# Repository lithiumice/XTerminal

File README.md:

## 说明
- 模拟器工程在XTerminal\2.Software\XTerminal-ESP32-simulator
- 模拟器工程使用Visual Studio 2019
- 代码工程在XTerminal\2.Software\XTerminal-ESP32-simulator
- 代码工程基于Platformio

#
PCB在项目工程的1.Hardware中，使用Kicad绘制。分为主控板和音频板，两者的硬件连接没有设计好，实际焊接为了便于组装就用了粗一点的飞线把主控板和音频板上的sd卡引脚和音频信号引脚连了起来，我只做了临时的用于验证的一个版本，后面没有心情完善了，只能说这只用于抛砖引玉。
#

#### 主控板焊接

#### 音频板焊接

#### 焊接和组装完成的成品效果：

#### 主界面：（没拍实物图，就只好放模拟器的截图了）

#### 天气显示：

#### 几个Arduboy小游戏

#### PCB示例

#### 原理图示例

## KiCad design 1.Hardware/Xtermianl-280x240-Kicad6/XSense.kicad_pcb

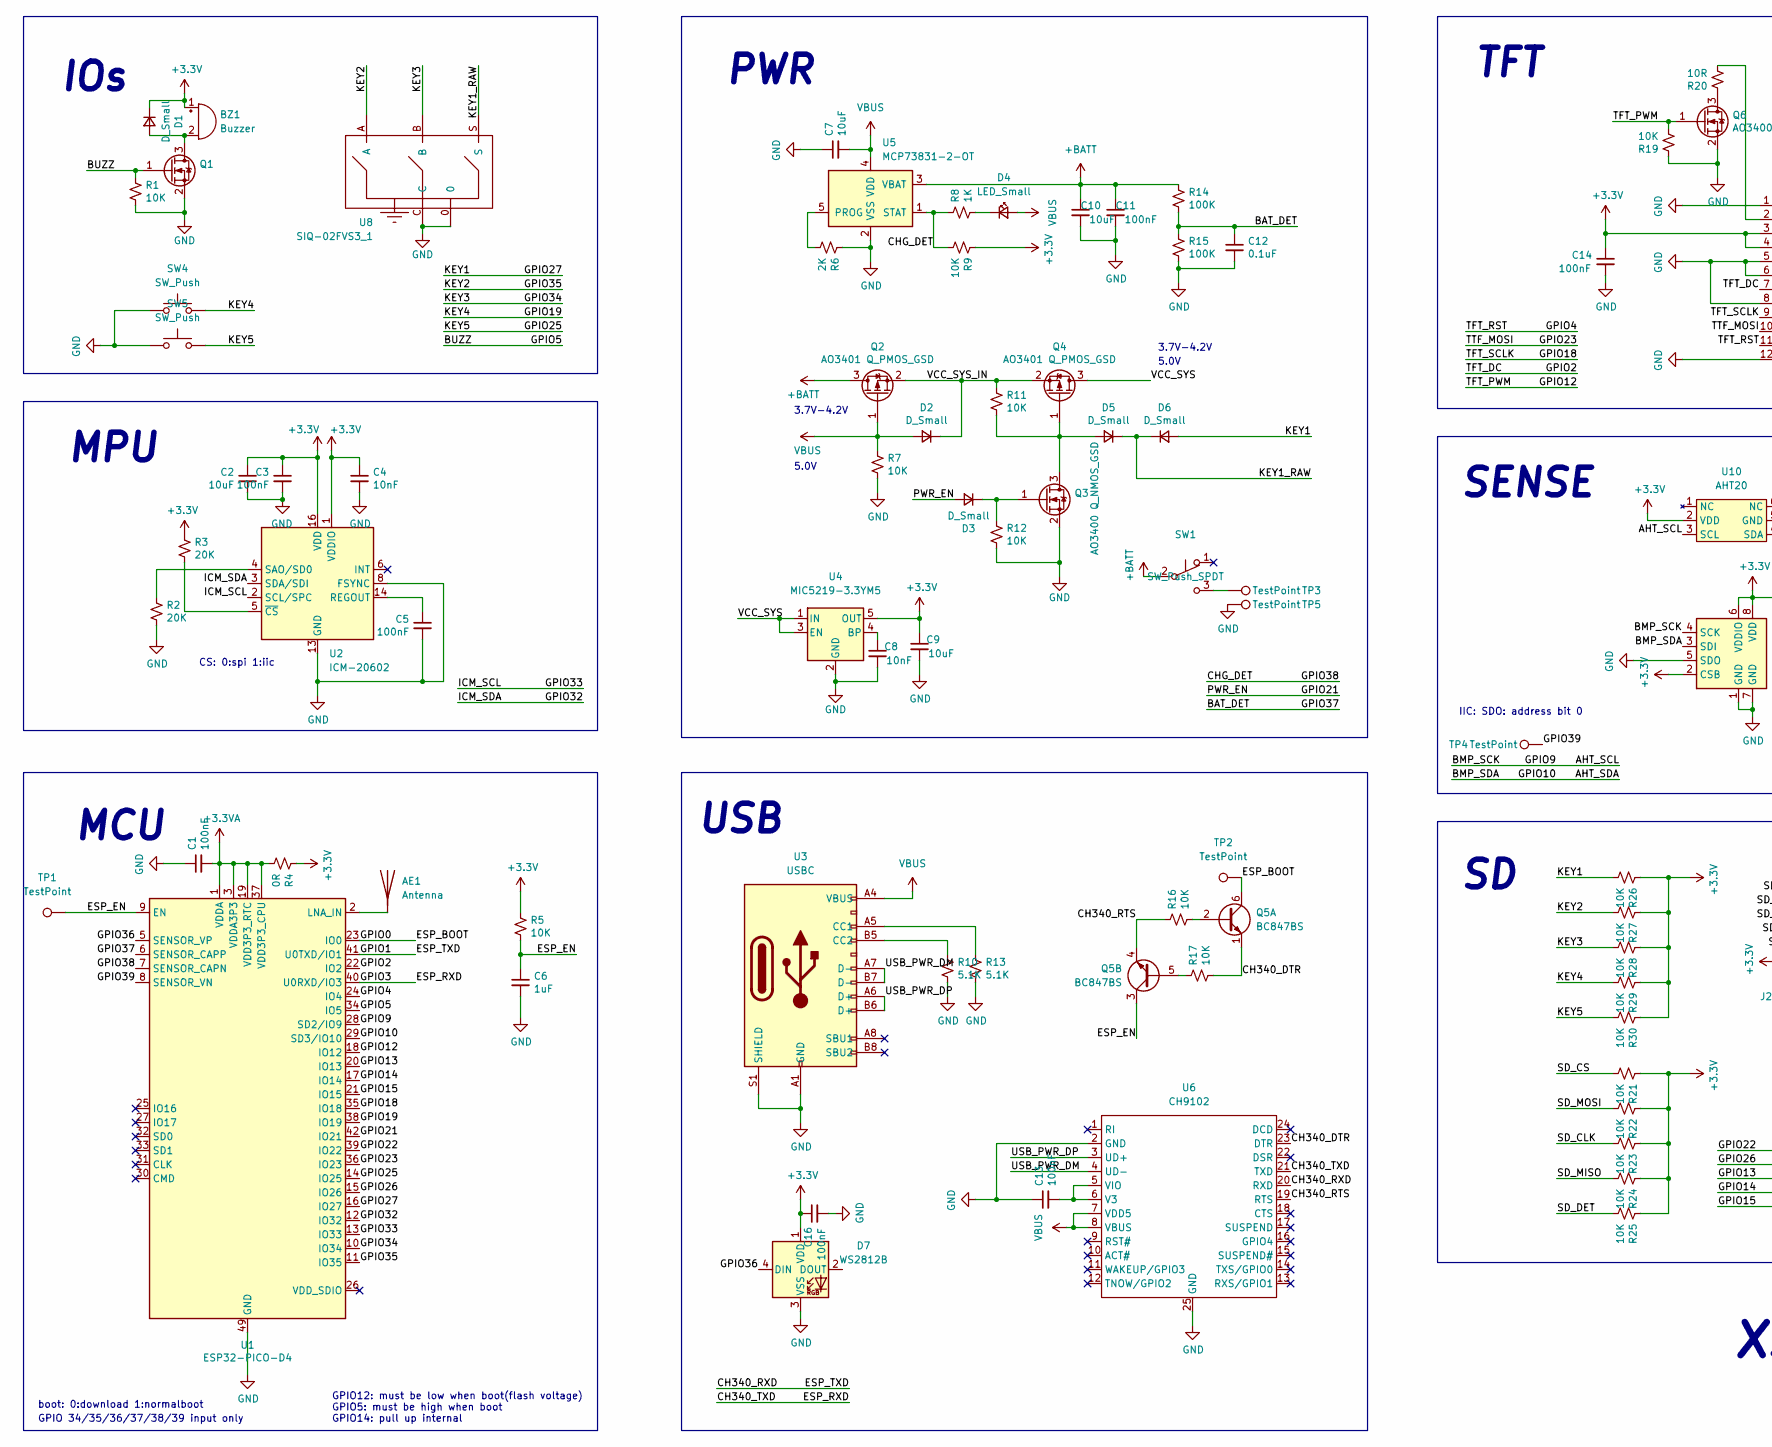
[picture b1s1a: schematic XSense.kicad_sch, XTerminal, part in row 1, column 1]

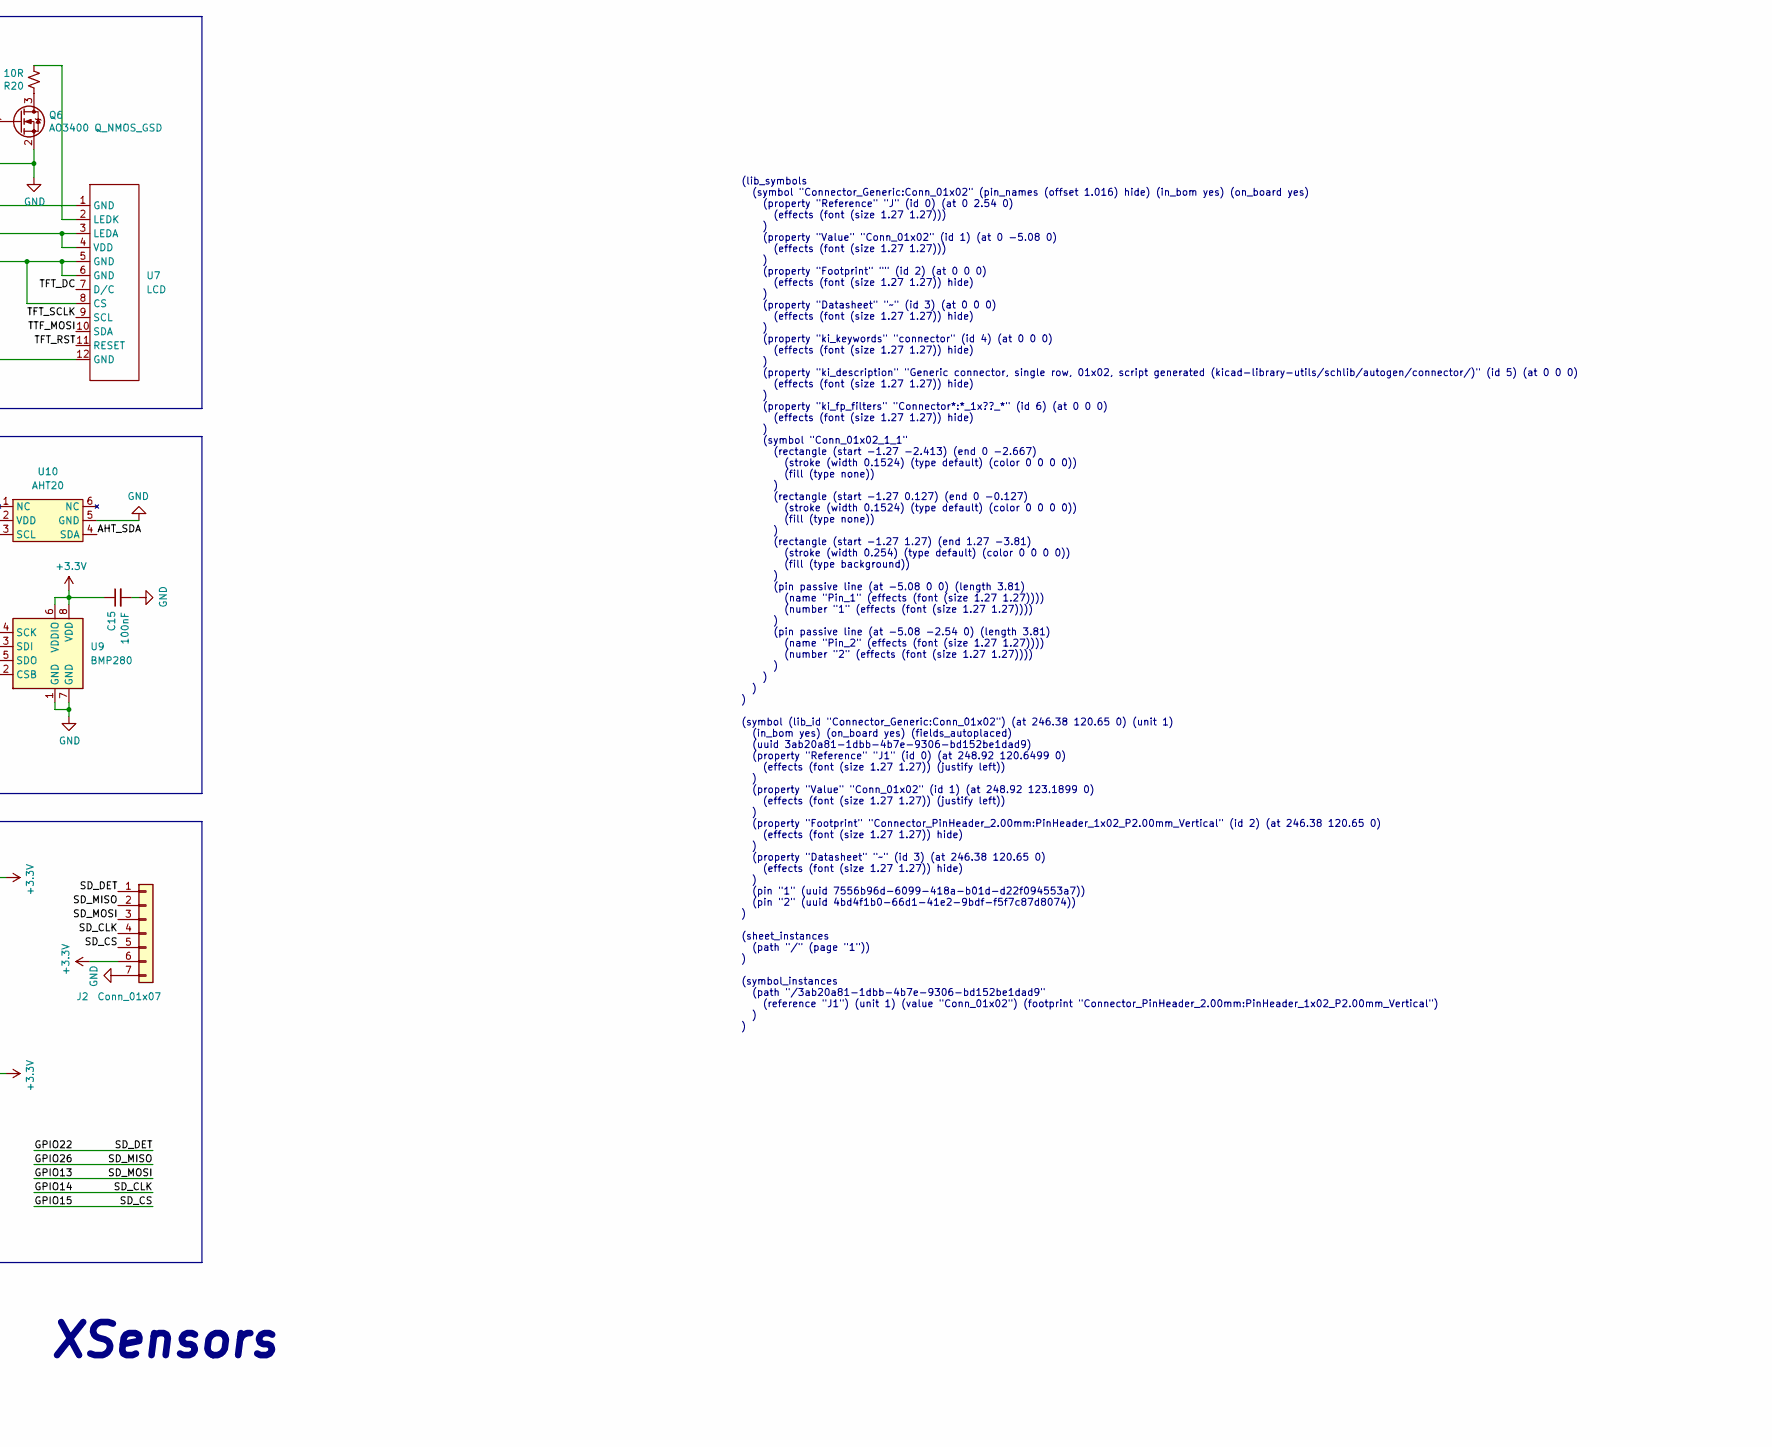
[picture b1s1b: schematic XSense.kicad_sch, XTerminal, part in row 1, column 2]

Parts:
AE1: Antenna; Johanson_2450AT43F0100
BZ1: Buzzer; DET402
C1, C3, C5, C11, C13, C14, C15, C16: 100nF; C_0402_1005Metric_Pad0.74x0.62mm_HandSolder
C2, C7, C9, C10: 10uF; C_0402_1005Metric_Pad0.74x0.62mm_HandSolder
C4, C8: 10nF; C_0402_1005Metric_Pad0.74x0.62mm_HandSolder
C6: 1uF; C_0402_1005Metric_Pad0.74x0.62mm_HandSolder
C12: 0.1uF; C_0402_1005Metric_Pad0.74x0.62mm_HandSolder
D1, D2, D3, D5, D6: D_Small; D_SOD-323
D4: LED_Small; C_0402_1005Metric_Pad0.74x0.62mm_HandSolder
D7: WS2812B; WS2812B-clear
J2: Conn_01x07; PinHeader_2x04_P2.00mm_Vertical
Q1, Q3, Q6: AO3400 Q_NMOS_GSD; SOT-23
Q2, Q4: AO3401 Q_PMOS_GSD; SOT-23
Q5: BC847BS; SOT-363_SC-70-6
R1, R5, R7, R9, R11, R12, R16, R17, R19, R21, R22, R23, R24, R25, R26, R27, R28, R29, R30: 10K; R_0402_1005Metric_Pad0.72x0.64mm_HandSolder
R2, R3: 20K; R_0402_1005Metric_Pad0.72x0.64mm_HandSolder
R4: 0R; R_0402_1005Metric_Pad0.72x0.64mm_HandSolder
R6: 2K; R_0402_1005Metric_Pad0.72x0.64mm_HandSolder
R8: 1K; R_0402_1005Metric_Pad0.72x0.64mm_HandSolder
R10, R13: 5.1K; R_0402_1005Metric_Pad0.72x0.64mm_HandSolder
R14, R15: 100K; R_0402_1005Metric_Pad0.72x0.64mm_HandSolder
R20: 10R; R_0402_1005Metric_Pad0.72x0.64mm_HandSolder
SW1: SW_Push_SPDT; SW_SPDT_PCM12
SW4, SW5: SW_Push; Panasonic_EVQPUJ_EVQPUA
TP1, TP2, TP3, TP4, TP5: TestPoint; TestPoint_Pad_D1.0mm
U1: ESP32-PICO-D4; QFN-48-7x7mm
U2: ICM-20602; LGA-16_3x3mm_P0.5mm_LayoutBorder3x5y
U3: USBC; USB_C_Receptacle_XKB_U262-16XN-4BVC11
U4: MIC5219-3.3YM5; SOT-23-5
U5: MCP73831-2-OT; SOT-23-5
U6: CH9102; QFN-24-1EP_4x4mm_P0.5mm_EP2.15x2.15mm
U7: LCD; LCD-ST7789-1.54-12PINS
U8: SIQ-02FVS3_1; SW-SMD_SIQ-02FVS3_1
U9: BMP280; Bosch_LGA-8_2x2.5mm_P0.65mm_ClockwisePinNumbering
U10: AHT20; DFN-6-1EP_3x3mm_P1mm_EP1.5x2.4mm

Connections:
+3.3VA: C1.2, R4.2, U1.1 (VDDA), U1.3 (VDDA3P3), U1.4 (VDDA3P3), U1.19 (VDD3P3_RTC), U1.37 (VDD3P3_CPU), U1.43 (VDDA), U1.46 (VDDA)
+3V3: BZ1.1 (-), C2.1, C3.1, C4.1, C9.1, C14.1, C15.1, C16.1, D1.1 (K), D7.1 (VDD), J2.6, R3.1, R4.1, R5.1, R9.1, R21.1, R22.1, R23.1, R24.1, R25.1, R26.1, R27.1, R28.1, R29.1, R30.1, U2.1 (VDDIO), U2.16 (VDD), U4.5 (OUT), U7.3 (LEDA), U7.4 (VDD), U9.2 (CSB), U9.6 (VDDIO), U9.8 (VDD), U10.2 (VDD)
+BATT: C10.1, C11.1, Q2.3 (D), R14.1, SW1.2 (B), U5.3 (VBAT)
/AHT_SCL: U1.28 (SD2/IO9), U9.4 (SCK), U10.3 (SCL)
/AHT_SDA: U1.29 (SD3/IO10), U9.3 (SDI), U10.4 (SDA)
/BAT_DET: C12.1, R14.2, R15.1, U1.6 (SENSOR_CAPP)
/BUZZ: Q1.1 (G), R1.1, U1.34 (IO5)
/CH340_DTR: Q5.1 (E1), R17.2, U6.23 (DTR)
/CH340_RTS: Q5.4 (E2), R16.1, U6.19 (RTS)
/CH340_RXD: U1.41 (U0TXD/IO1), U6.20 (RXD)
/CH340_TXD: U1.40 (U0RXD/IO3), U6.21 (TXD)
/CHG_DET: R8.1, R9.2, U1.7 (SENSOR_CAPN), U5.1 (STAT)
/ESP_BOOT: Q5.6 (C1), TP2.1, U1.23 (IO0)
/ESP_EN: C6.1, Q5.3 (C2), R5.2, TP1.1, U1.9 (EN)
/GPIO2: U1.22 (IO2), U7.7 (D/C)
/GPIO4: U1.24 (IO4), U7.11 (RESET)
/GPIO12: Q6.1 (G), R19.2, U1.18 (IO12)
/GPIO13: J2.3, R22.2, U1.20 (IO13)
/GPIO14: J2.4, R23.2, U1.17 (IO14)
/GPIO15: J2.5, R21.2, U1.21 (IO15)
/GPIO18: U1.35 (IO18), U7.9 (SCL)
/GPIO19: R29.2, SW4.2, U1.38 (IO19)
/GPIO21: D3.2 (A), U1.42 (IO21)
/GPIO22: J2.1, R25.2, U1.39 (IO22)
/GPIO23: U1.36 (IO23), U7.10 (SDA)
/GPIO25: R30.2, SW5.2, U1.14 (IO25)
/GPIO26: J2.2, R24.2, U1.15 (IO26)
/GPIO27: D6.2 (A), R26.2, U1.16 (IO27)
/GPIO32: U1.12 (IO32), U2.3 (SDA/SDI)
/GPIO33: U1.13 (IO33), U2.2 (SCL/SPC)
/GPIO34: R28.2, U1.10 (IO34), U8.B
/GPIO35: R27.2, U1.11 (IO35), U8.A
/GPIO36: D7.4 (DIN), U1.5 (SENSOR_VP)
/GPIO39: TP4.1, U1.8 (SENSOR_VN)
/KEY1_RAW: D5.1 (K), D6.1 (K), U8.S
/USB_PWR_DM: U3.A7 (D-), U3.B7 (D-), U6.4 (UD-)
/USB_PWR_DP: U3.A6 (D+), U3.B6 (D+), U6.3 (UD+)
/VCC_SYS: Q4.3 (D), U4.1 (IN), U4.3 (EN)
/VCC_SYS_IN: D2.1 (K), Q2.2 (S), Q4.2 (S), R11.1
GND: C1.1, C2.2, C3.2, C4.2, C5.2, C6.2, C7.1, C8.2, C9.2, C10.2, C11.2, C12.2, C13.1, C14.2, C15.2, C16.2, D7.3 (VSS), J2.7, Q1.2 (S), Q3.2 (S), Q6.2 (S), R1.2, R2.2, R6.1, R7.2, R10.2, R12.2, R13.2, R15.2, R19.1, SW4.1, SW5.1, TP5.1, U1.49 (GND), U2.8 (FSYNC), U2.9 (GND), U2.10 (GND), U2.11 (GND), U2.12 (GND), U2.13 (GND), U2.15 (GND), U3.A1 (GND), U3.A12 (GND), U3.B1 (GND), U3.B12 (GND), U3.S1 (SHIELD), U4.2 (GND), U5.2 (VSS), U6.2 (GND), U6.25 (GND), U7.1 (GND), U7.5 (GND), U7.6 (GND), U7.8 (CS), U7.12 (GND), U8.0, U8.C, U9.1 (GND), U9.5 (SDO), U9.7 (GND), U10.5 (GND)
unnamed: AE1.1 (A), U1.2 (LNA_IN)
unnamed: BZ1.2 (+), D1.2 (A), Q1.3 (D)
unnamed: C5.1, U2.14 (REGOUT)
unnamed: C8.1, U4.4 (BP)
unnamed: C13.2, U6.5 (VIO), U6.6 (V3)
unnamed: D3.1 (K), Q3.1 (G), R12.1
unnamed: D4.1 (K), R8.2
unnamed: D5.2 (A), Q3.3 (D), Q4.1 (G), R11.2
unnamed: Q5.2 (B1), R16.2
unnamed: Q5.5 (B2), R17.1
unnamed: Q6.3 (D), R20.1
unnamed: R2.1, U2.4 (SAO/SD0)
unnamed: R3.2, U2.5 (~CS)
unnamed: R6.2, U5.5 (PROG)
unnamed: R10.1, U3.B5 (CC2)
unnamed: R13.1, U3.A5 (CC1)
unnamed: R20.2, U7.2 (LEDK)
unnamed: SW1.3 (C), TP3.1
VBUS: C7.2, D2.2 (A), D4.2 (A), Q2.1 (G), R7.1, U3.A4 (VBUS), U3.A9 (VBUS), U3.B4 (VBUS), U3.B9 (VBUS), U5.4 (VDD), U6.7 (VDD5), U6.8 (VBUS)

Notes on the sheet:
MPU
GPIO 34/35/36/37/38/39 input only
(lib_symbols (symbol "Connector_Generic:Conn_01x02" (pin_names (offset 1.016) hide) (in_bom yes) (on_board yes) (property "Reference" "J" (id 0) (at 0 2.54 0) (effects (font (size 1.27 1.27))) ) (property "Value" "Conn_01x02" (id 1) (at 0 -5.08 0) (effects (font (size 1.27 1.27))) ) (property "Foot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
IIC: SDO: address bit 0
5.0V
3.7V-4.2V
GPIO12: must be low when boot(flash voltage) GPIO5: must be high when boot GPIO14: pull up internal
XSensors
MCU
USB
PWR
IOs
boot: 0:download 1:normalboot
SENSE
TFT
CS: 0:spi 1:iic

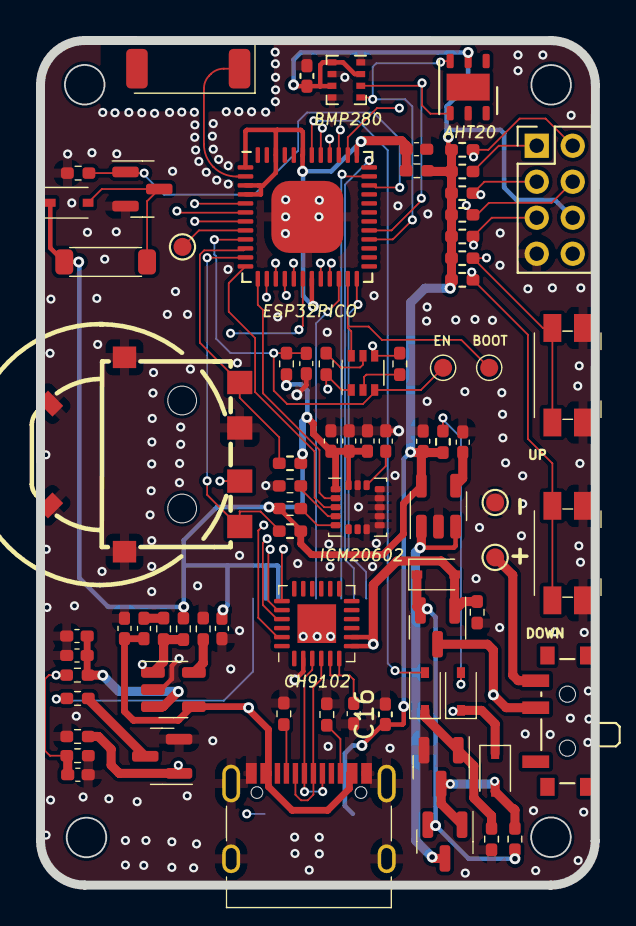
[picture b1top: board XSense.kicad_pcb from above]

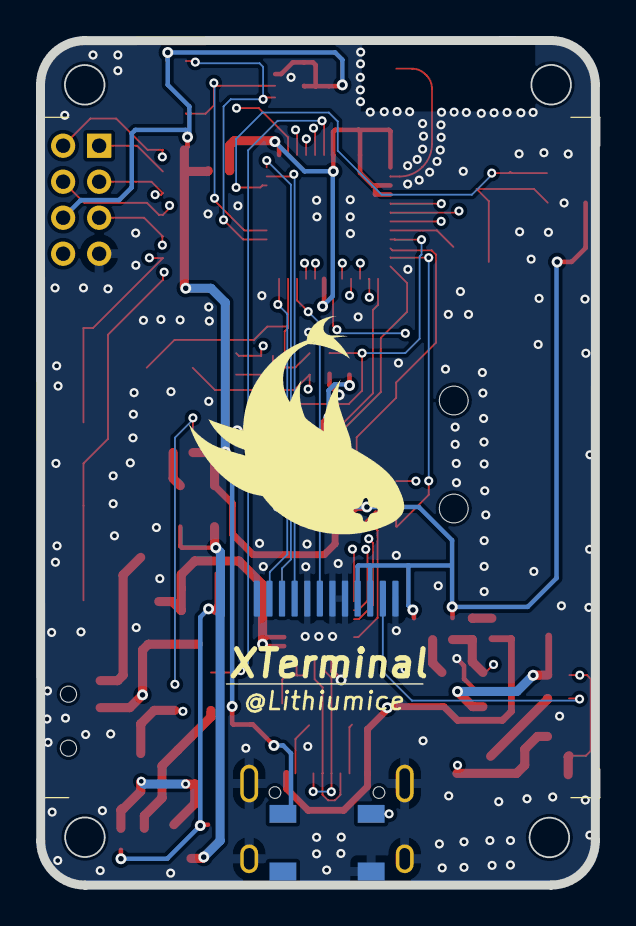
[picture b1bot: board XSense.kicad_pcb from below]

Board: 4 copper layers, 30.8 x 46.9 mm, 79 parts (2 on the bottom side), 59 nets.

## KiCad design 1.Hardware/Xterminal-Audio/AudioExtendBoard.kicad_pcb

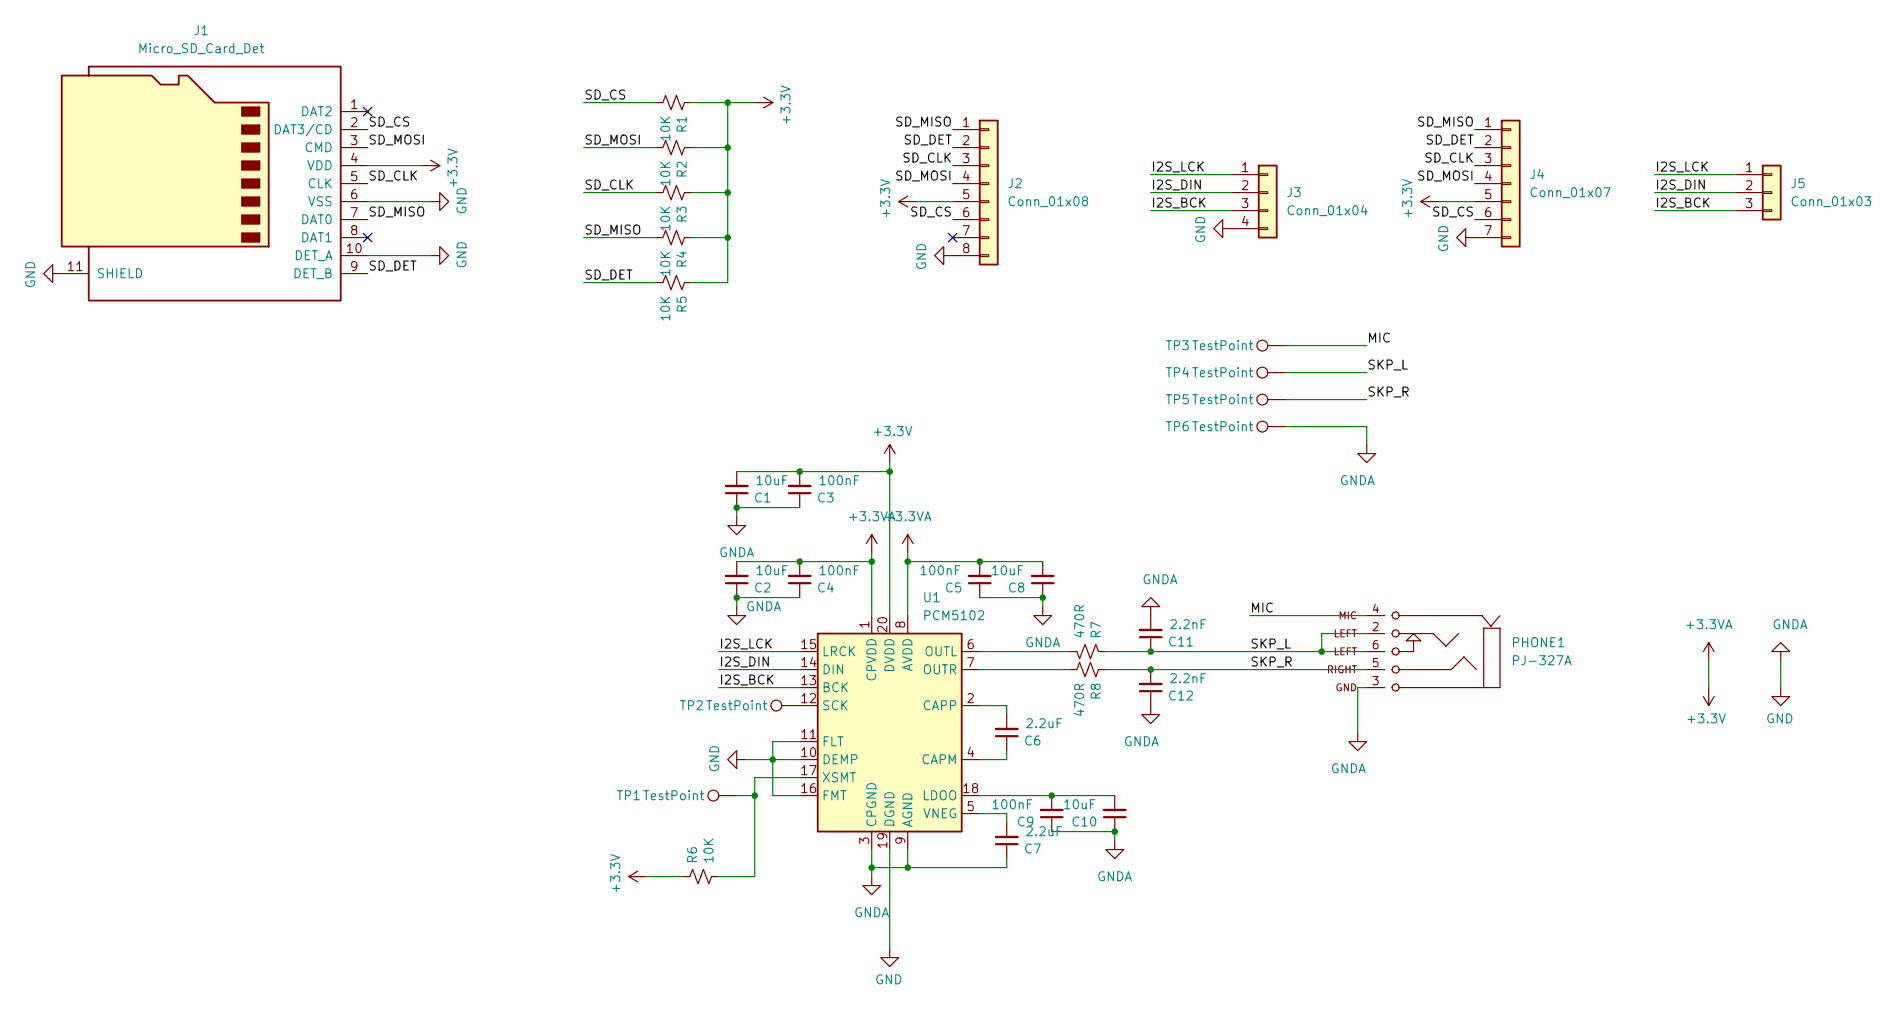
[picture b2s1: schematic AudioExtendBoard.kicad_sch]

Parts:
C1, C2, C8, C10: 10uF; C_0402_1005Metric_Pad0.74x0.62mm_HandSolder
C3, C4, C5, C9: 100nF; C_0402_1005Metric_Pad0.74x0.62mm_HandSolder
C6, C7: 2.2uF; C_0402_1005Metric_Pad0.74x0.62mm_HandSolder
C11, C12: 2.2nF; C_0402_1005Metric_Pad0.74x0.62mm_HandSolder
J1: Micro_SD_Card_Det; TF-SMD_TF-015
J2: Conn_01x08; PinHeader_2x04_P2.00mm_Vertical
J3: Conn_01x04; PinHeader_1x04_P2.00mm_Vertical
J4: Conn_01x07; Molex_CLIK-Mate_502382-0770_1x07-1MP_P1.25mm_Vertical
J5: Conn_01x03; Molex_CLIK-Mate_502382-0370_1x03-1MP_P1.25mm_Vertical
PHONE1: PJ-327A; PJ327A
R1, R2, R3, R4, R5, R6: 10K; R_0402_1005Metric_Pad0.72x0.64mm_HandSolder
R7, R8: 470R; R_0402_1005Metric_Pad0.72x0.64mm_HandSolder
TP1, TP2, TP3, TP4, TP5, TP6: TestPoint; TestPoint_Pad_D1.0mm
U1: PCM5102; TSSOP-20_4.4x6.5mm_P0.65mm

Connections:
+3.3VA: C1.2, C2.2, C3.2, C4.2, C5.2, C8.2, J1.4 (VDD), J2.5, J4.5, R1.1, R2.1, R3.1, R4.1, R5.1, R6.1, U1.1 (CPVDD), U1.8 (AVDD), U1.20 (DVDD)
/I2S_BCK: J3.3, J5.3, U1.13 (BCK)
/I2S_DIN: J3.2, J5.2, U1.14 (DIN)
/I2S_LCK: J3.1, J5.1, U1.15 (LRCK)
/MIC: PHONE1.4, TP3.1
/SD_CLK: J1.5 (CLK), J2.3, J4.3, R3.2
/SD_CS: J1.2 (DAT3/CD), J2.6, J4.6, R1.2
/SD_DET: J1.9 (DET_B), J2.2, J4.2, R5.2
/SD_MISO: J1.7 (DAT0), J2.1, J4.1, R4.2
/SD_MOSI: J1.3 (CMD), J2.4, J4.4, R2.2
/SKP_L: C11.1, PHONE1.2, PHONE1.6, R7.1, TP4.1
/SKP_R: C12.2, PHONE1.5, R8.1, TP5.1
GND: C1.1, C2.1, C3.1, C4.1, C5.1, C7.1, C8.1, C9.1, C10.1, C11.2, C12.1, J1.6 (VSS), J1.10 (DET_A), J1.11 (SHIELD), J2.8, J3.4, J4.7, PHONE1.3 (1), TP6.1, U1.3 (CPGND), U1.9 (AGND), U1.10 (DEMP), U1.11 (FLT), U1.16 (FMT), U1.19 (DGND)
unnamed: C6.1, U1.4 (CAPM)
unnamed: C6.2, U1.2 (CAPP)
unnamed: C7.2, U1.5 (VNEG)
unnamed: C9.2, C10.2, U1.18 (LDOO)
unnamed: R6.2, TP1.1, U1.17 (XSMT)
unnamed: R7.2, U1.6 (OUTL)
unnamed: R8.2, U1.7 (OUTR)
unnamed: TP2.1, U1.12 (SCK)

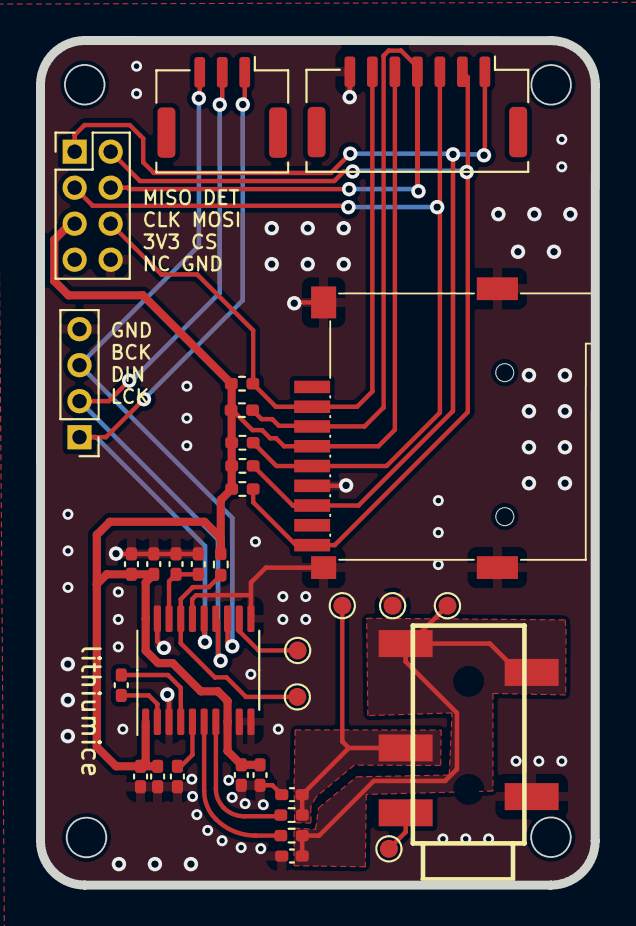
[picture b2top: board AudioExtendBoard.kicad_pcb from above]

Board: 2 copper layers, 30.8 x 46.9 mm, 33 parts (0 on the bottom side), 21 nets.

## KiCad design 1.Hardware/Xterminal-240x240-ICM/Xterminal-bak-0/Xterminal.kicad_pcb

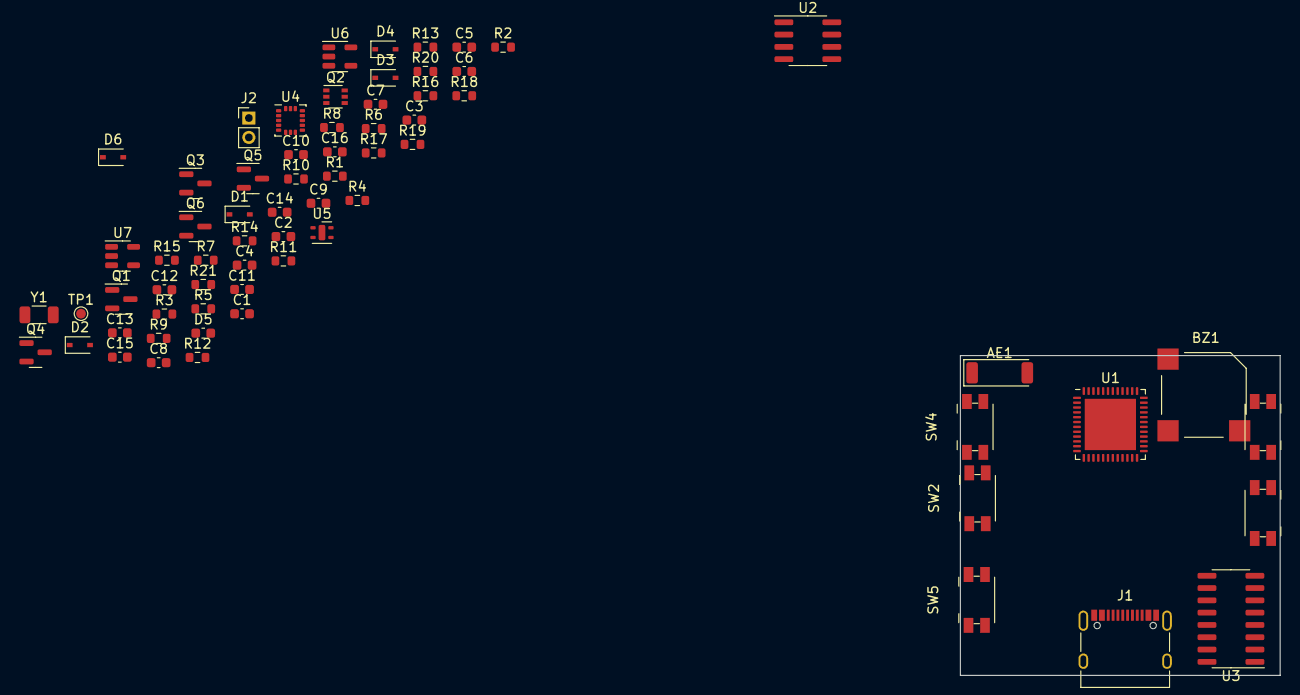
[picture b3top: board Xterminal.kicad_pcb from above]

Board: 2 copper layers, 33.0 x 33.0 mm, 68 parts (1 on the bottom side), 56 nets, no tracks yet.

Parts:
AE1: Antenna; Johanson_2450AT43F0100
BZ1: Buzzer; MagneticBuzzer_Kobitone_254-EMB84Q-RO
C1, C2, C3, C4, C6, C13, C15, C16: 100nF; C_0603_1608Metric
C5: 2.2uF; C_0603_1608Metric
C7, C10: 10nF; C_0603_1608Metric
C8: 1uF; C_0603_1608Metric
C9, C11, C12: 10uF; C_0603_1608Metric
C14: 0.1uF; C_0603_1608Metric
D1, D2, D3, D4, D6: D_Small; D_SOD-323
D5: LED_Small; C_0603_1608Metric
J1: USB_C_Receptacle; USB_C_Receptacle_XKB_U262-16XN-4BVC11
J2: Conn_01x02; PinHeader_1x02_P2.00mm_Vertical
Q1, Q4: AO3401 Q_PMOS_GSD; SOT-23
Q2: BC847BS; SOT-363_SC-70-6
Q3, Q5, Q6: AO3400 Q_NMOS_GSD; SOT-23
R1, R4, R5, R6, R19: 20K; R_0603_1608Metric
R2, R7, R11, R13, R16, R17, R18, R20: 10K; R_0603_1608Metric
R3: 0R; R_0603_1608Metric
R8: 2K; R_0603_1608Metric
R9, R10: 5.1K; R_0603_1608Metric
R12: 1K; R_0603_1608Metric
R14, R15: 100K; R_0603_1608Metric
R21: 10R; R_0603_1608Metric
SW1, SW2, SW3, SW4, SW5: SW_Push; Panasonic_EVQPUJ_EVQPUA
TP1: TestPoint; TestPoint_Pad_D1.0mm
U1: ESP32-PICO-D4; QFN-48-1EP_7x7mm_P0.5mm_EP5.3x5.3mm
U2: PCF8563T; SOIC-8_3.9x4.9mm_P1.27mm
U3: CH340C; SOIC-16_3.9x9.9mm_P1.27mm
U4: ICM-20602; LGA-16_3x3mm_P0.5mm_LayoutBorder3x5y
U5: SHTC3; Sensirion_DFN-4-1EP_2x2mm_P1mm_EP0.7x1.6mm
U6: MIC5219-3.3YM5; SOT-23-5
U7: MCP73831-2-OT; SOT-23-5
U8: LCD; LCD-ST7789-1.54-12PINS
Y1: Crystal_Small; R_1206_3216Metric

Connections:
+3.3VA: C4.2, R3.2, U1.1 (VDDA), U1.3 (VDDA3P3), U1.4 (VDDA3P3), U1.19 (VDD3P3_RTC), U1.37 (VDD3P3_CPU), U1.43 (VDDA), U1.46 (VDDA)
+3V3: BZ1.1 (-), C3.1, C5.1, C6.1, C7.1, C11.1, C15.1, C16.1, D6.1 (K), R2.1, R3.1, R4.1, R7.1, R13.1, R18.1, U2.8 (VDD), U3.4 (V3), U3.16 (VCC), U4.1 (VDDIO), U4.16 (VDD), U5.1 (VDD), U6.5 (OUT), U8.3 (LEDA), U8.4 (VDD)
+BATT: C12.1, C13.1, J2.1, Q1.3 (D), R14.1, U7.3 (VBAT)
/BAT_DET: C14.1, R14.2, R15.1, U1.6 (SENSOR_CAPP)
/BUZZ: Q5.1 (G), R19.1, U1.14 (IO25)
/CH340_DTR: Q2.1 (E1), R17.2, U3.13 (~DTR)
/CH340_RTS: Q2.4 (E2), R16.1, U3.14 (~RTS)
/CH340_RXD: U1.41 (U0TXD/IO1), U3.3 (RXD)
/CH340_TXD: U1.40 (U0RXD/IO3), U3.2 (TXD)
/CHG_DET: R12.1, R13.2, U1.7 (SENSOR_CAPN), U7.1 (STAT)
/ESP_BOOT: Q2.6 (C1), U1.23 (IO0)
/ESP_EN: C8.1, Q2.3 (C2), R7.2, TP1.1, U1.9 (EN)
/GPIO2: U1.22 (IO2), U8.7 (D/C)
/GPIO4: U1.24 (IO4), U8.11 (RESET)
/GPIO5: SW5.2, U1.34 (IO5)
/GPIO9: U1.28 (SD2/IO9), U2.6 (SCL)
/GPIO10: U1.29 (SD3/IO10), U2.5 (SDA)
/GPIO12: Q6.1 (G), R20.2, U1.18 (IO12)
/GPIO13: R2.2, U1.20 (IO13), U2.7 (CLKO)
/GPIO14: U1.17 (IO14), U2.3 (~INT)
/GPIO15: U1.21 (IO15), U5.2 (SCL)
/GPIO18: U1.35 (IO18), U8.9 (SCL)
/GPIO19: U1.38 (IO19), U5.3 (SDA)
/GPIO21: D2.2 (A), U1.42 (IO21)
/GPIO23: U1.36 (IO23), U8.10 (SDA)
/GPIO27: D4.2 (A), R18.2, U1.16 (IO27)
/GPIO32: U1.12 (IO32), U4.3 (SDA/SDI)
/GPIO33: U1.13 (IO33), U4.2 (SCL/SPC)
/GPIO34: U1.10 (IO34), U4.6 (INT)
/GPIO35: SW2.2, U1.11 (IO35)
/KEY1_RAW: D3.1 (K), D4.1 (K), SW1.2
/KEY3: SW3.2, U1.39 (IO22)
/KEY4: SW4.2, U1.15 (IO26)
/USB_PWR_DM: J1.A7 (D-), J1.B7 (D-), U3.6 (UD-)
/USB_PWR_DP: J1.A6 (D+), J1.B6 (D+), U3.5 (UD+)
/VCC_SYS: Q4.2 (S), U6.1 (IN), U6.3 (EN)
/VCC_SYS_IN: D1.1 (K), Q1.2 (S), Q4.3 (D), R6.1
GND: C1.1, C2.1, C3.2, C4.1, C5.2, C6.2, C7.2, C8.2, C9.1, C10.2, C11.2, C12.2, C13.2, C14.2, C15.2, C16.2, J1.A1 (GND), J1.A12 (GND), J1.B1 (GND), J1.B12 (GND), J1.S1 (SHIELD), J2.2, Q3.2 (S), Q5.2 (S), Q6.2 (S), R1.2, R5.2, R8.1, R9.2, R10.2, R11.2, R15.2, R19.2, R20.1, SW1.1, SW2.1, SW3.1, SW4.1, SW5.1, U1.49 (GND), U3.1 (GND), U4.8 (FSYNC), U4.9 (GND), U4.10 (GND), U4.11 (GND), U4.12 (GND), U4.13 (GND), U4.15 (GND), U5.4 (VSS), U6.2 (GND), U7.2 (VSS), U8.1 (GND), U8.5 (GND), U8.6 (GND), U8.8 (CS), U8.12 (GND)
unnamed: AE1.1 (A), U1.2 (LNA_IN)
unnamed: BZ1.2 (+), D6.2 (A), Q5.3 (D)
unnamed: C1.2, U2.1 (OSCI), Y1.2
unnamed: C2.2, U2.2 (OSCO), Y1.1
unnamed: C10.1, U6.4 (BP)
unnamed: D2.1 (K), Q3.1 (G), R5.1
unnamed: D3.2 (A), Q3.3 (D), Q4.1 (G), R6.2
unnamed: D5.1 (K), R12.2
unnamed: J1.A5 (CC1), R10.1
unnamed: J1.B5 (CC2), R9.1
unnamed: Q2.2 (B1), R16.2
unnamed: Q2.5 (B2), R17.1
unnamed: Q6.3 (D), R21.1
unnamed: R1.1, U4.4 (SAO/SD0)
unnamed: R4.2, U4.5 (~CS)
unnamed: R8.2, U7.5 (PROG)
unnamed: R21.2, U8.2 (LEDK)
VBUS: C9.2, D1.2 (A), D5.2 (A), J1.A4 (VBUS), J1.A9 (VBUS), J1.B4 (VBUS), J1.B9 (VBUS), Q1.1 (G), R11.1, U7.4 (VDD)

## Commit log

2022-01-10 init
2022-03-14 intergrate partments
2022-03-14 update readme && merge firmware
